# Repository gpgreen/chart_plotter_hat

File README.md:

# Chart Plotter Hat

KiCad design for Raspberry Pi Hat. Provides power and switch on/off
for the board. A total of 1.2A is provided for use by the
RaspberryPi. Also some connectors for GPS, barometric sensor, and ADC
measurements. Provides 12V power for a remote video board which is
switched at the same time as the Raspberry Pi. Contains a MCP2515 CAN
Controller and MCP2551 CAN transceiver for access to CAN bus. The
transceiver is isolated from the rest of the board. Has a
 connector that allows I2C
devices to be connected to the Raspberry Pi.

## Functions

1. Onboard ATmega328P
2. 1.2A DC power for RaspberryPi provided by
   
3. Video board power (12V) controlled by solid state relay G3VM-201FR
4. Serial Connector for GPS with 5V power, routed to Raspberry Pi Uart1.
5. 2 connectors with 4 pins each routed to adc pins on ATmega328P
6. Qwiic Connector, routed to I2C1 on Raspberry Pi
7. eeprom & power isolation as required by Raspberry Pi hat spec
8. Onboard 3.3V power for the ATmega328P.
9. SPI on ATmega328P routed to the Raspberry Pi SPI0 for communication
10. MCP2515 CAN network device, controlled by Raspberry Pi on SPI1
11. CAN is isolated to meet specs of NMEA 2000.
12. Connector for external voltmeter, or see 13.
13. Optional 12V voltage divider routed to ADC7 on the ATmega328P. This option is
    selected by a solder jumper.

## Firmware

There are 2 projects for the firmware. One is using `C`, the other `Rust`.
 -  for the
onboard ATmega328P using avr-gcc and avr-libc.
 - .

The Rust firmware is still experimental. There are a number of
compiler bugs for the 8-bit AVR's yet.

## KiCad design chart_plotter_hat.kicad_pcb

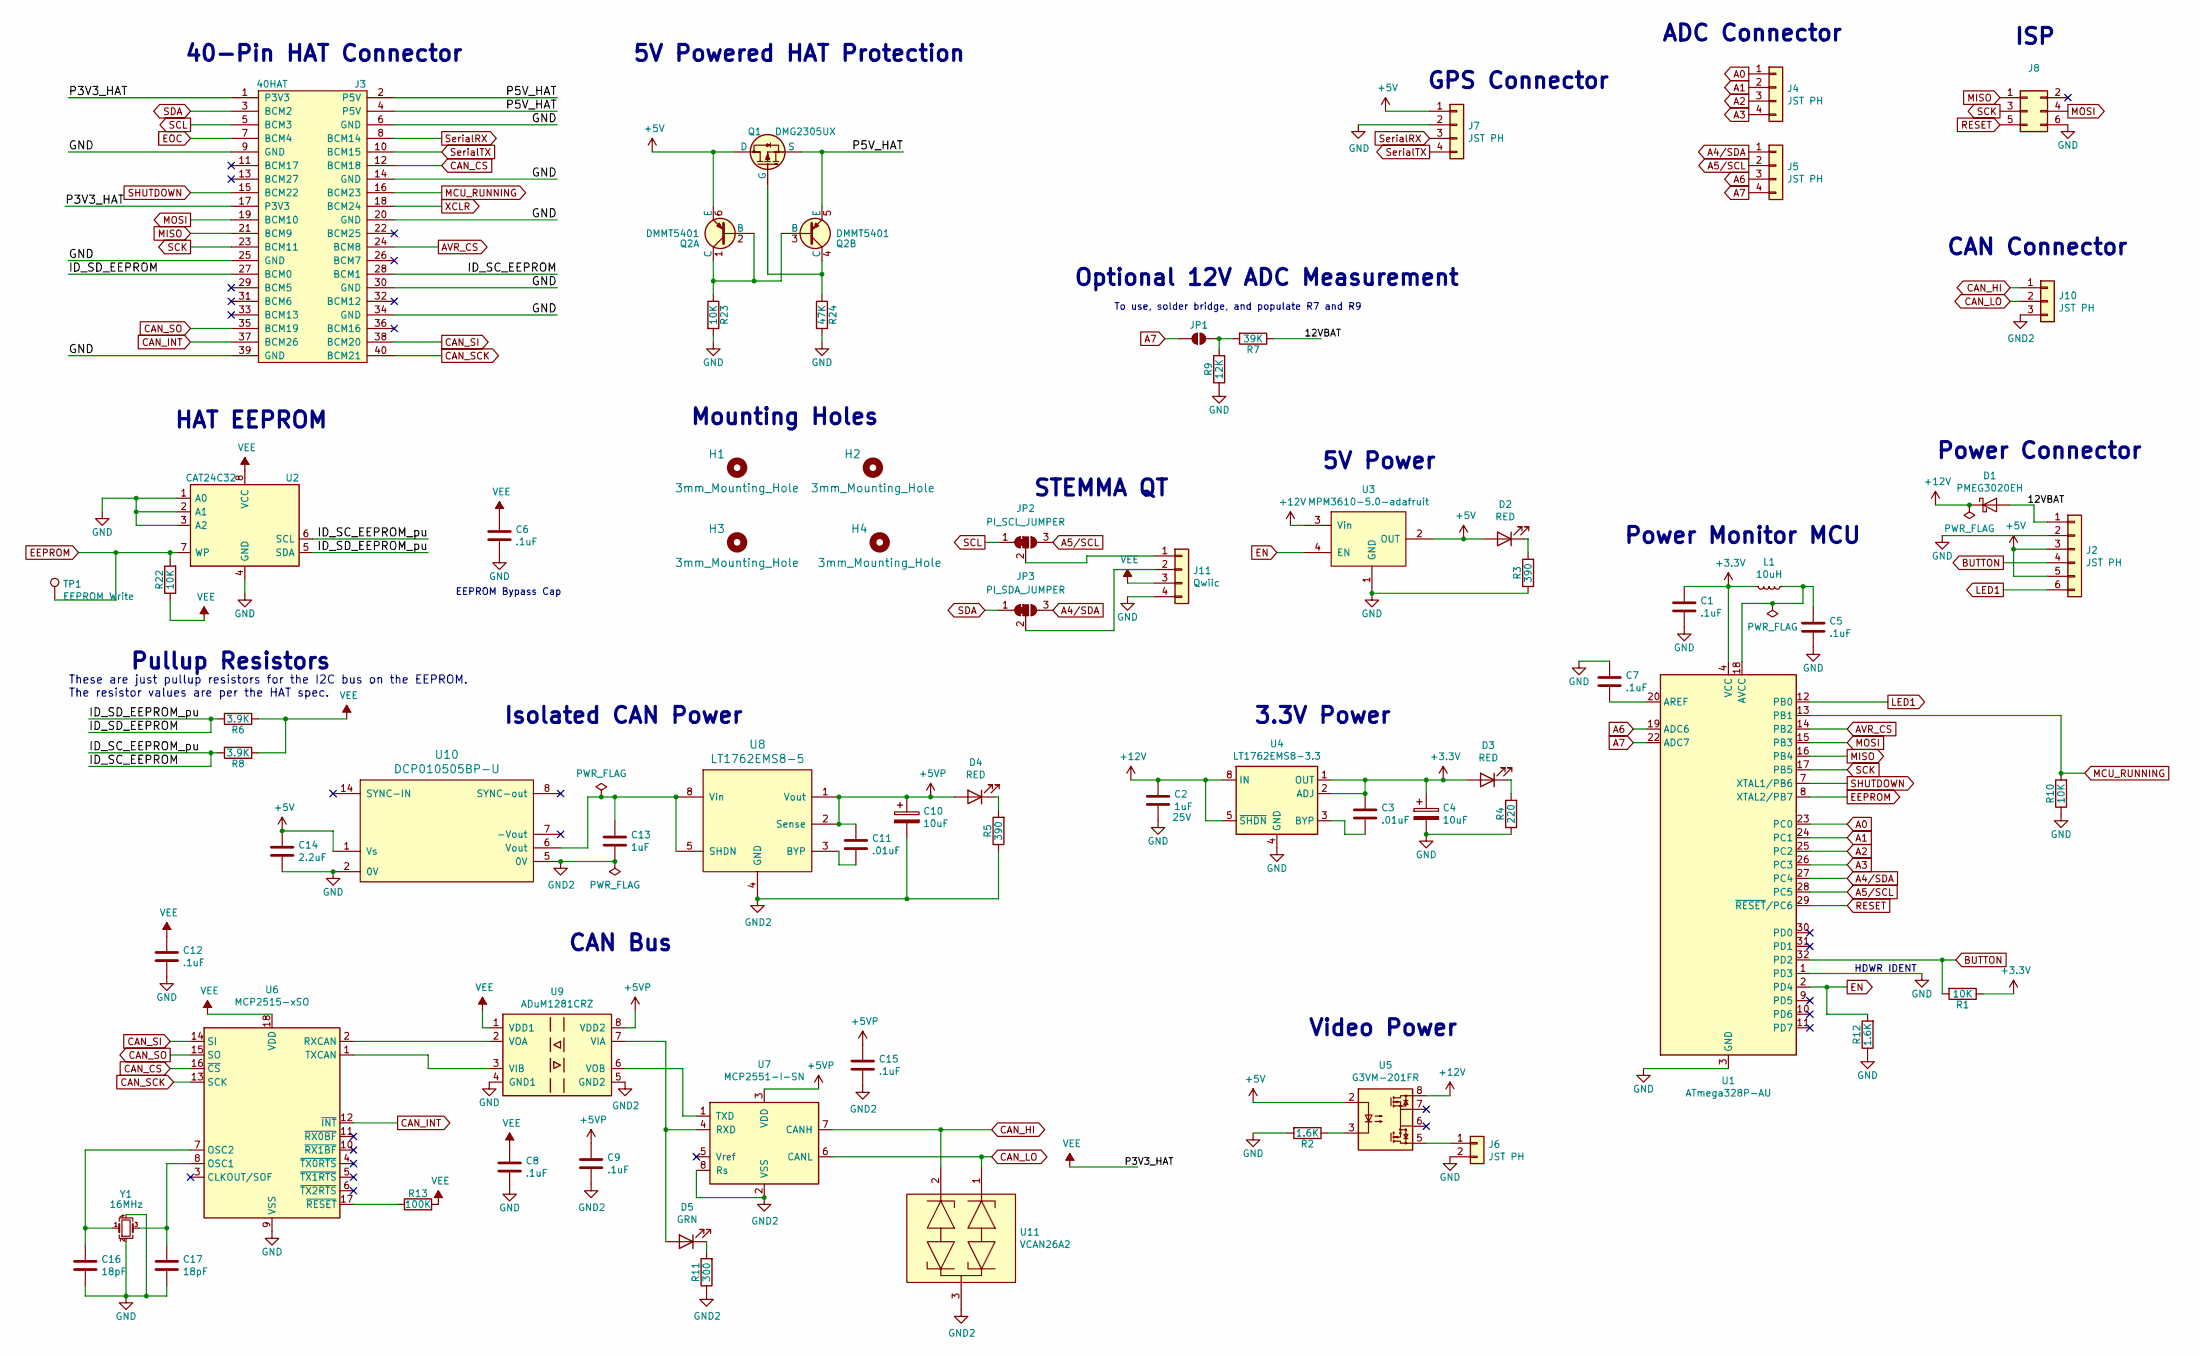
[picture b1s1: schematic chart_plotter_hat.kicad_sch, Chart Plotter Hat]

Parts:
C1, C5, C6, C7, C8, C9, C12, C15: .1uF; C_0603
C2: 1uF; C_1206; Voltage 25V
C3, C11: .01uF; C_0603
C4, C10: 10uF; CP_Tantalum_Case-A_EIA-3216-18_Reflow
C13: 1uF; C_1206
C14: 2.2uF; C_1206
C16, C17: 18pF; C_0603
D1: PMEG3020EH; D_SOD-123
D2, D3, D4: RED; D_0603
D5: GRN; D_0603
H1, H2, H3, H4: 3mm_Mounting_Hole; NPTH_3mm_ID
J2: JST PH; JST_PH_B6B-PH-K_06x2.00mm_Straight
J3: 40HAT; PinSocket_2x20_P2.54mm_Vertical
J4, J5, J7: JST PH; JST_PH_B4B-PH-K_04x2.00mm_Straight
J6: JST PH; JST_PH_B2B-PH-K_02x2.00mm_Straight
J8: Conn_02x03_Odd_Even; Pin_Header_Straight_2x03_Pitch2.54mm
J10: JST PH; JST_PH_B3B-PH-K_03x2.00mm_Straight
J11: Qwiic; JST_SH_BM04B-SRSS-TB_04x1.00mm_Straight
JP1: SolderJumper_2_Open; SolderJumper-2_P1.3mm_Open_RoundedPad1.0x1.5mm
JP2: PI_SCL_JUMPER; SolderJumper-3_P1.3mm_Bridged2Bar12_Pad1.0x1.5mm
JP3: PI_SDA_JUMPER; SolderJumper-3_P1.3mm_Bridged2Bar12_Pad1.0x1.5mm
L1: 10uH; C_0603
Q1: DMG2305UX; SOT-23
Q2: DMMT5401; SOT-23-6
R1, R10, R22, R23: 10K; R_0603
R2, R12: 1.6K; R_0603
R3, R5: 390; R_0603
R4: 220; R_0603
R6, R8: 3.9K; R_0603
R7: 39K; R_0603
R9: 12K; R_0603
R11: 300; R_0603
R13: 100K; R_0603
R24: 47K; R_0603
TP1: EEPROM Write; Measurement_Point_Square-SMD-Pad_Small
U1: ATmega328P-AU; TQFP-32_7x7mm_Pitch0.8mm
U2: CAT24C32; SOIC-8_3.9x4.9mm_P1.27mm
U3: MPM3610-5.0-adafruit; Adafruit_MPM3610
U4: LT1762EMS8-3.3; MSOP-8_3x3mm_Pitch0.65mm
U5: G3VM-201FR; DIP-8_W8.89mm_SMDSocket_LongPads
U6: MCP2515-xSO; SOIC-18W_7.5x11.6mm_Pitch1.27mm
U7: MCP2551-I-SN; SOIC-8_3.9x4.9mm_Pitch1.27mm
U8: LT1762EMS8-5; MSOP-8_3x3mm_Pitch0.65mm
U9: ADuM1281CRZ; SOIC-8_3.9x4.9mm_Pitch1.27mm
U10: DCP010505BP-U; DCP01B_SO_7_14
U11: VCAN26A2; SOT-323_SC-70
Y1: 16MHz; Crystal_SMD_TXC_7M-4pin_3.2x2.5mm

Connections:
+3.3V: C1.1, C3.1, C4.1, D3.2 (A), L1.2, R1.1, U1.4 (VCC), U1.6 (VCC), U4.1 (OUT), U4.2 (ADJ)
+5V: C14.1, D2.2 (A), J2.3, J2.5, J7.1, Q1.3 (D), Q2.6 (E), U3.2 (OUT), U5.2, U10.1 (Vs)
+5VP: C9.1, C10.1, C11.1, C15.1, D4.2 (A), U7.3 (VDD), U8.1 (Vout), U8.2 (Sense), U9.8 (VDD2)
+12V: C2.1, D1.1 (K), U3.3 (Vin), U4.5 (~SHDN), U4.8 (IN), U5.8
/12VBAT: D1.2 (A), J2.1, R7.1
/ID_SC_EEPROM: J3.28 (BCM1), R8.2, U2.6 (SCL)
/ID_SD_EEPROM: J3.27 (BCM0), R6.2, U2.5 (SDA)
/P5V_HAT: J3.2 (P5V), J3.4 (P5V), Q1.2 (S), Q2.5 (E)
A0: J4.1, U1.23 (PC0)
A1: J4.2, U1.24 (PC1)
A2: J4.3, U1.25 (PC2)
A3: J4.4, U1.26 (PC3)
A4/SDA: J5.1, JP3.3 (B), U1.27 (PC4)
A5/SCL: J5.2, JP2.3 (B), U1.28 (PC5)
A6: J5.3, U1.19 (ADC6)
A7: J5.4, JP1.1 (A), U1.22 (ADC7)
AVR_CS: J3.24 (BCM8), U1.14 (PB2)
BUTTON: J2.4, R1.2, U1.32 (PD2)
CAN_CS: J3.12 (BCM18), U6.16 (~CS)
CAN_HI: J10.1, U7.7 (CANH), U11.2
CAN_INT: J3.37 (BCM26), U6.12 (~INT)
CAN_LO: J10.2, U7.6 (CANL), U11.1
CAN_SCK: J3.40 (BCM21), U6.13 (SCK)
CAN_SI: J3.38 (BCM20), U6.14 (SI)
CAN_SO: J3.35 (BCM19), U6.15 (SO)
EEPROM: R22.2, TP1.1, U1.8 (XTAL2/PB7), U2.7 (WP)
EN: R12.2, U1.2 (PD4), U3.4 (EN)
EOC: J3.7 (BCM4)
GND: C1.2, C2.2, C4.2, C5.2, C6.2, C7.1, C8.2, C12.2, C14.2, C16.2, C17.2, J2.2, J3.6 (GND), J3.9 (GND), J3.14 (GND), J3.20 (GND), J3.25 (GND), J3.30 (GND), J3.34 (GND), J3.39 (GND), J6.2, J7.2, J8.6, J11.4, R2.2, R3.1, R4.1, R9.1, R10.1, R12.1, R23.2, R24.2, U1.1 (PD3), U1.3 (GND), U1.5 (GND), U1.21 (GND), U2.1 (A0), U2.2 (A1), U2.3 (A2), U2.4 (GND), U3.1 (GND), U4.4 (GND), U6.9 (VSS), U9.4 (GND1), U10.2 (0V), Y1.2, Y1.4
GND2: C9.2, C10.2, C13.2, C15.2, J10.3, R5.1, R11.1, U7.2 (VSS), U7.8 (Rs), U8.4 (GND), U9.5 (GND2), U10.5 (0V), U11.3
LED1: J2.6, U1.12 (PB0)
MCU_RUNNING: J3.16 (BCM23), R10.2, U1.13 (PB1)
MISO: J3.21 (BCM9), J8.1, U1.16 (PB4)
MOSI: J3.19 (BCM10), J8.4, U1.15 (PB3)
unnamed: D2.1 (K), R3.2
unnamed: D3.1 (K), R4.2
unnamed: D4.1 (K), R5.2
unnamed: D5.2 (A), U7.4 (RXD), U9.7 (VIA)
unnamed: D5.1 (K), R11.2
unnamed: J6.1, U5.5
unnamed: J11.1, JP2.2 (C)
unnamed: J11.2, JP3.2 (C)
unnamed: JP1.2 (B), R7.2, R9.2
unnamed: Q1.1 (G), Q2.4 (C), R24.1
unnamed: Q2.1 (C), Q2.2 (B), Q2.3 (B), R23.1
unnamed: R2.1, U5.3
unnamed: C7.2, U1.20 (AREF)
unnamed: C5.1, L1.1, U1.18 (AVCC)
unnamed: C3.2, U4.3 (BYP)
unnamed: C17.1, U6.8 (OSC1), Y1.3
unnamed: C16.1, U6.7 (OSC2), Y1.1
unnamed: U6.2 (RXCAN), U9.2 (VOA)
unnamed: U6.1 (TXCAN), U9.3 (VIB)
unnamed: R13.1, U6.17 (~RESET)
unnamed: U7.1 (TXD), U9.6 (VOB)
unnamed: C11.2, U8.3 (BYP)
unnamed: C13.1, U8.5 (SHDN), U8.8 (Vin), U10.6 (Vout)
RESET: J8.5, U1.29 (~RESET/PC6)
SCK: J3.23 (BCM11), J8.3, U1.17 (PB5)
SCL: J3.5 (BCM3), JP2.1 (A)
SDA: J3.3 (BCM2), JP3.1 (A)
SHUTDOWN: J3.15 (BCM22), U1.7 (XTAL1/PB6)
SerialRX: J3.8 (BCM14), J7.3
SerialTX: J3.10 (BCM15), J7.4
VEE: C6.1, C8.1, C12.1, J3.1 (P3V3), J3.17 (P3V3), J11.3, R6.1, R8.1, R13.2, R22.1, U2.8 (VCC), U6.18 (VDD), U9.1 (VDD1)
XCLR: J3.18 (BCM24)

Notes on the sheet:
3.3V Power
HAT EEPROM
5V Power
CAN Bus
These are just pullup resistors for the I2C bus on the EEPROM. The resistor values are per the HAT spec.
EEPROM Bypass Cap
Mounting Holes
To use, solder bridge, and populate R7 and R9
40-Pin HAT Connector
GPS Connector
Optional 12V ADC Measurement
Video Power
ADC Connector
5V Powered HAT Protection
Pullup Resistors
ISP
STEMMA QT
Isolated CAN Power
CAN Connector
Power Monitor MCU
HDWR IDENT
Power Connector

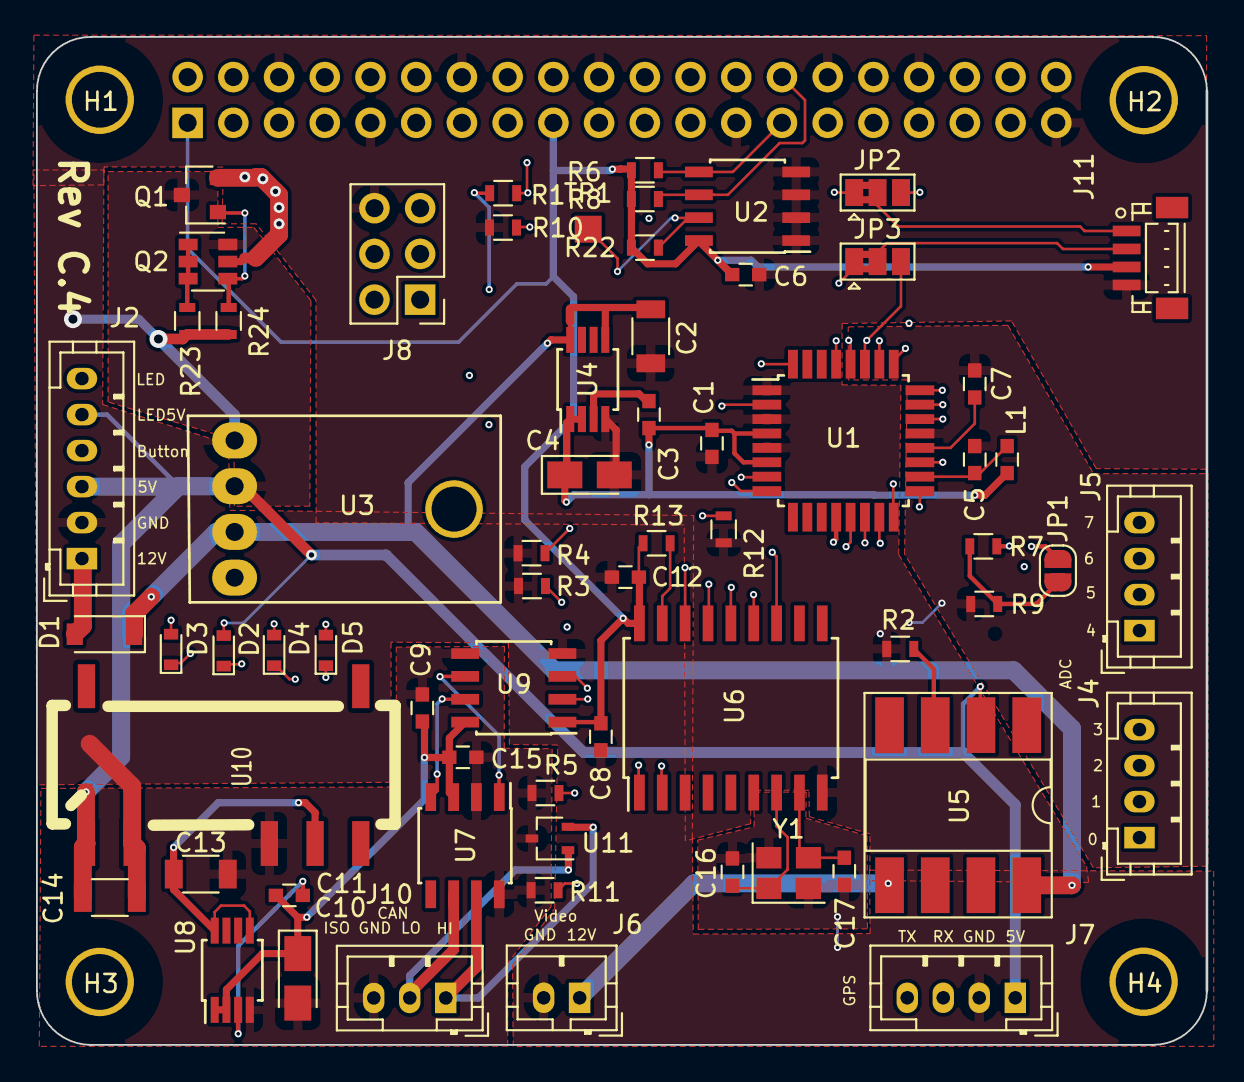
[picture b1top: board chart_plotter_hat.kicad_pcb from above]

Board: 4 copper layers, 65.0 x 55.9 mm, 70 parts (1 on the bottom side), 64 nets.

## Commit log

2020-12-15 many changes
2020-12-15 Changed SS relay to a G3VM-201FR
2020-12-16 Changed footprints to non-solder
    changed headers to JST-PH connectors
    changed mask clearance
    Connected EOC
2020-12-18 MCU_RUNNING was connected to P3.3V on header
    Moved MCU_RUNNING to a gpio pin
2020-12-19 Initial Layout after adding mcp2515
2020-12-19 Using buffer chips instead of fet
2020-12-28 Updated layout using mcp2515 and buffers
2020-12-28 Added README and board graphic
2020-12-29 Added pulldown resistor to MCU_RUNNING
2020-12-29 Added pulldown R10 on MCU_RUNNING
2021-01-02 Fixed relay net
2021-01-02 Fixed relay wiring
2021-01-02 Updated board pix
2021-01-02 Moved R2 resistor to ground side of relay circuit
2021-01-02 Moved second led to MISO instead of shutdown
    Cleaned up some via's
2021-01-03 Redid relay wiring
2021-01-04 Added voltmeter connection
    Added reverse polarity protection diode
    Moved non-power LED to it's own pin
    Added R5, SHUTDOWN pull-down resistor
2021-01-04 Added Inductor to AVCC
    Added optional 12VBAT adc on A7
    Changed P5V label to +5V
2021-01-04 Added pdf of original release
2021-01-04 Added ADC ground plane
2021-01-06 Moved CS to PD3, MCU_RUNNING to PB1
    Renamed SS to CS
2021-01-07 Removed pull down on SHUTDOWN, not needed
2021-01-10 Routed BUTTON to the Pi also
2021-01-16 Removed Jumper2, don't need
2021-02-15 Referenced rust firmware project
    Updated resistor values
2021-04-10 Updated from rev B
2021-04-10 First pass at layout
2021-04-12 Fixed 3.3aux switch and mounting hole sizes
2021-04-19 Added CAN_RST pull-ups
2021-04-24 Crystal was miswired
    Replaced schematic symbol for Y1
    Rewired Y1 in pcb
2021-08-15 Added optical isolation in CAN
2021-08-21 Redid CAN isolation, removed level shifter
2021-08-25 Updated README
    Created pdf of schematic, updated board graphic
2021-09-06 Added power isolation to CAN
    TVS added to CAN output
    DCP01B used for power isolation from board
    Another LT1762 used for CAN isolation power
    Removed pull-ups from CAN controller, should be controlled by Pi
    Added LED's for hat pwr, pi pwr, CAN isolation pwr, and CAN Rx
    Reordered connections on Power connector
2021-09-08 Renamed some resistors
    Changed resistor value from 180 to 220, to match inventory
2021-09-08 Updated schematic pdf
    Changed drawing size to US Ledger, instead of A3
2021-09-08 Fixed bom to match schematic
2021-09-17 Added DS1307 RTC
    Added coin cell battery holder
    updated bom
2021-09-18 Removed DS1307, (Not avail), added STEMMA QT conx
    can connect an adafruit breakout board for RTC instead
2021-09-28 Removed 6 pin J1, replaced with 2 pin J1
    barometer databus now goes through qwiic connector, only
    interrupt lines are in J1
2022-03-21 updated board.png and bom.ods
2022-06-29 Added R12 pull-down to EN, jumper for eeprom write
2022-06-30 Added pullup on CAN RST, removed jumper on EEPROM write
2022-07-01 Removed pullup on CANRST, connected to 3.3V instead
2022-07-02 Added resistor between 3.3 and CAN RST
2022-07-22 qwik pcb connections were backwards, fixed
2022-08-08 Changed MCU to attiny261
2025-10-14 Updated files for kicad 6
2025-10-14 Updated files for newer kicad
2025-10-14 Added solder jumpers for SCL/SDA
    Removed BMP connector and associated routes
    Can now connect QWIK connector to Pi or Atmega via jumpers
2025-10-14 Removed voltmeter connector and traces
    Updated some trace routing
2025-11-01 Release of Rev C.4
2025-11-01 Update of README, pix for cph
